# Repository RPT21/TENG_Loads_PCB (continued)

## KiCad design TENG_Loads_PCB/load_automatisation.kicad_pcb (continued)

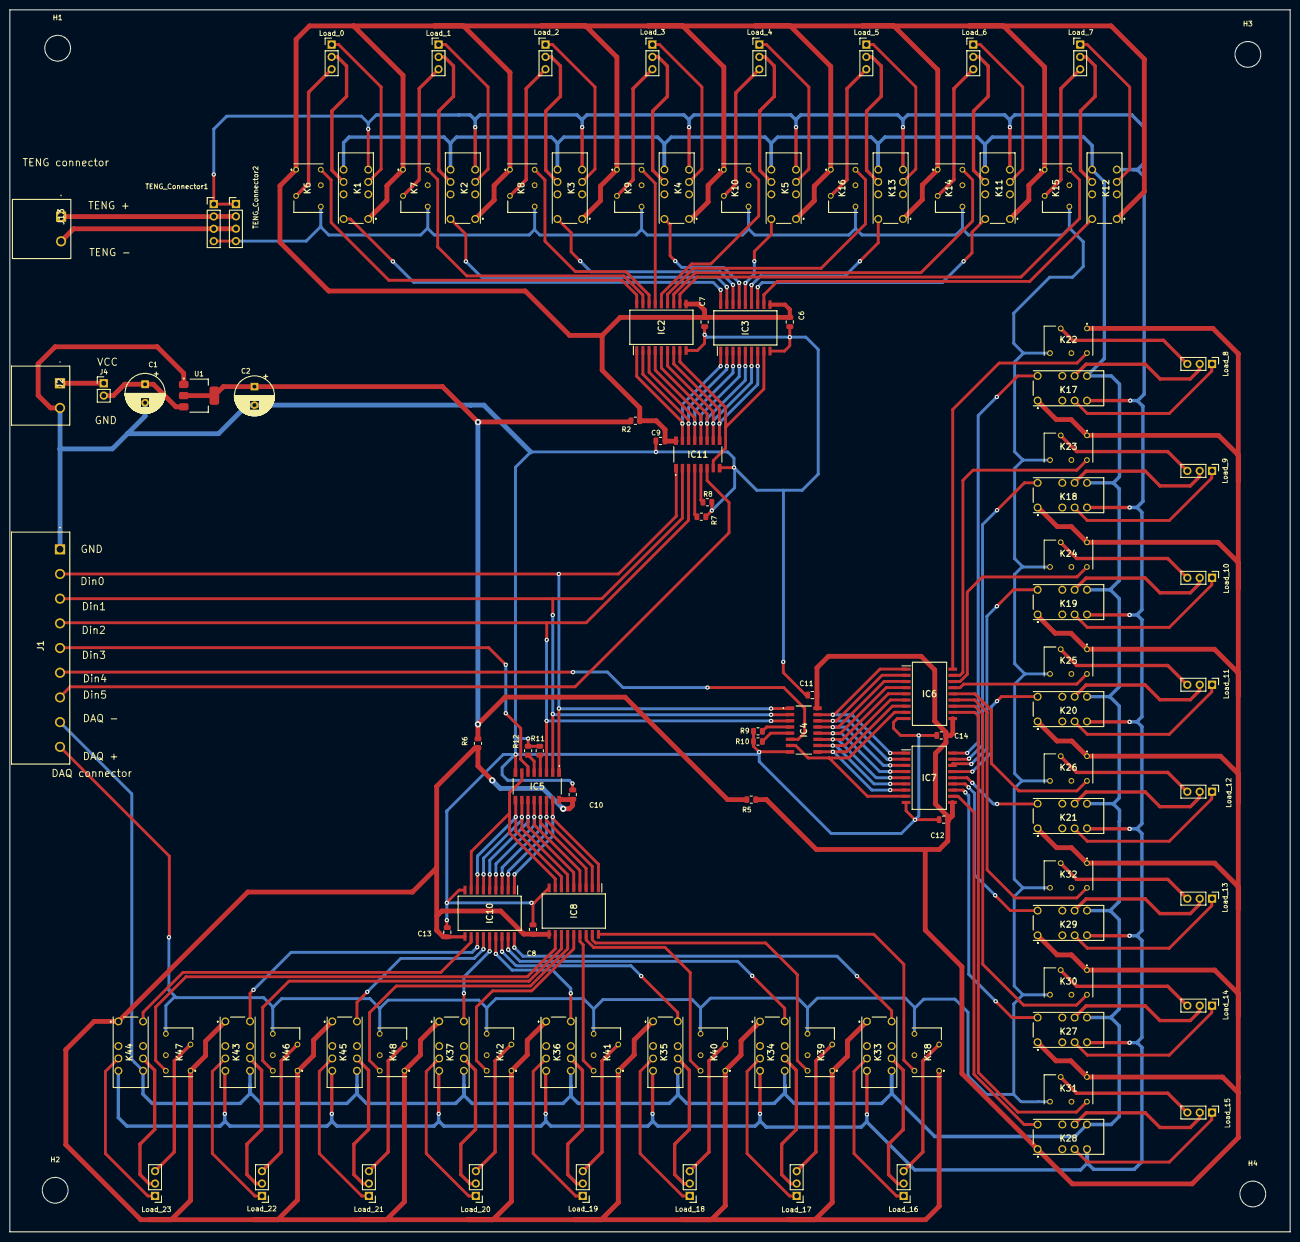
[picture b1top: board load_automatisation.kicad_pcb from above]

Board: 2 copper layers, 263.4 x 251.4 mm, 112 parts (0 on the bottom side), 168 nets.

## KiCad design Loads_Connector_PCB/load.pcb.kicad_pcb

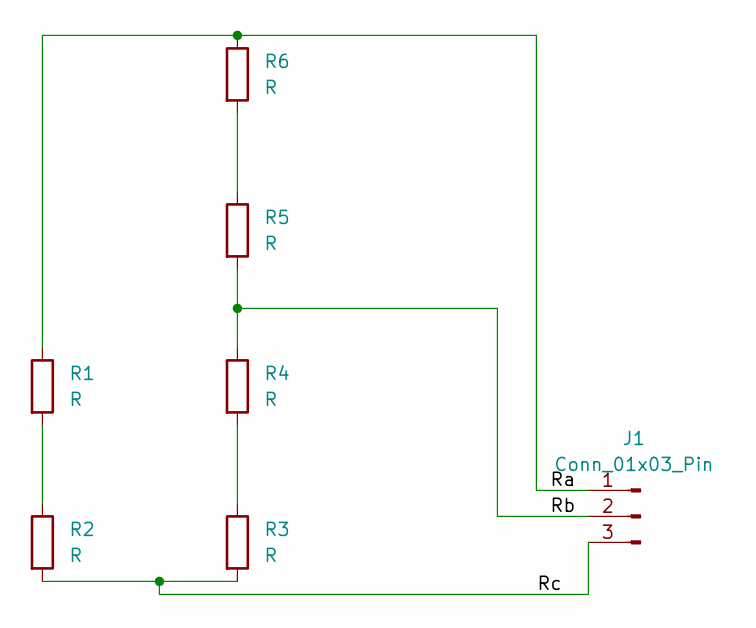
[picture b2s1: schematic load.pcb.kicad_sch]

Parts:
J1: Conn_01x03_Pin; PinHeader_1x03_P2.54mm_Horizontal
R1: R; R_Axial_DIN0614_L14.3mm_D5.7mm_P20.32mm_Horizontal
R2, R3, R4, R5, R6: R; R_0805_2012Metric

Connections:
/Ra: J1.1, R1.1, R6.1
/Rb: J1.2, R4.1, R5.2
/Rc: J1.3, R2.2, R3.2
unnamed: R1.2, R2.1
unnamed: R3.1, R4.2
unnamed: R5.1, R6.2

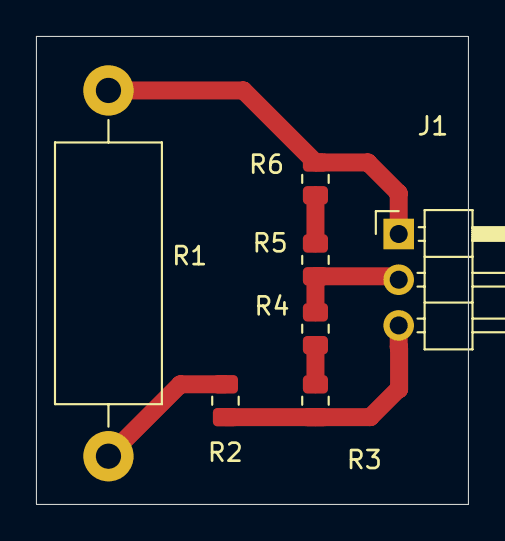
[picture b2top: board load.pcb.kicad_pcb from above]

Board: 2 copper layers, 24.0 x 26.0 mm, 7 parts (0 on the bottom side), 6 nets.

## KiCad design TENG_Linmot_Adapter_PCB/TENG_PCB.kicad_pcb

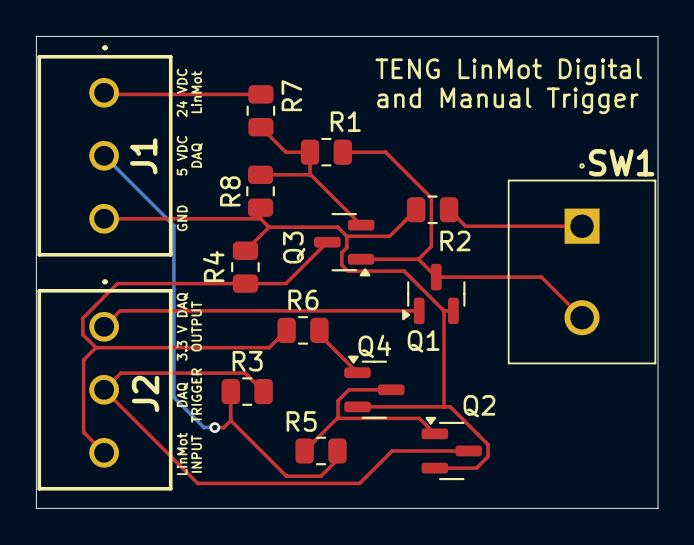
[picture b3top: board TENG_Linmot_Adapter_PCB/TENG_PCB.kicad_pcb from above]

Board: 2 copper layers, 34.5 x 26.2 mm, 15 parts (0 on the bottom side), 11 nets.

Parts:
J1, J2: 1751251
Q1, Q2, Q4: ZVN3310F; SOT-23
Q3: ZVP3310F; SOT-23
R1, R4, R6: 200K; R_0805_2012Metric
R2: 10K; R_0805_2012Metric
R3, R5: 100K; R_0805_2012Metric
R7: 5k; R_0805_2012Metric
R8: 15k; R_0805_2012Metric
SW1: SW_DIP_x01; 1729128

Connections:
5VDC_DAQ: J1.2, R3.1, R5.1
18VDC: Q3.2 (S), R1.1, R7.2, R8.1
+24V: J1.1, R7.1
DAQ_OUT_3.3V: J2.1, Q1.1 (G)
DAQ_TRIGGER: J2.2, Q2.3 (D), R3.2
GND: J1.3, Q1.2 (S), Q2.2 (S), Q4.2 (S), R2.2, R4.2, R8.2
LinMot_IN: J2.3, Q3.3 (D), R4.1, R6.1
unnamed: Q1.3 (D), Q3.1 (G), R1.2, SW1.2
unnamed: Q2.1 (G), Q4.3 (D), R5.2
unnamed: Q4.1 (G), R6.2
unnamed: R2.1, SW1.1

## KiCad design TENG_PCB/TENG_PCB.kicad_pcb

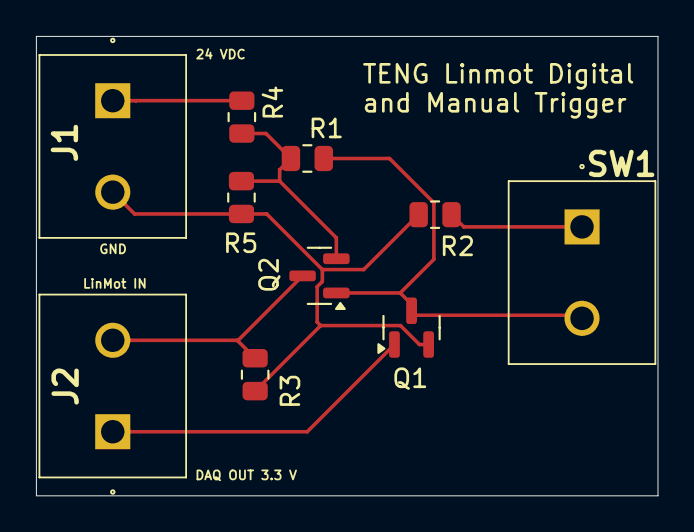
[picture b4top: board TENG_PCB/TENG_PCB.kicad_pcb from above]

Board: 2 copper layers, 34.5 x 25.5 mm, 10 parts (0 on the bottom side), 7 nets.

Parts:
J1, J2: 1729128
Q1: ZVN3310F; SOT-23
Q2: ZVP3310F; SOT-23
R1, R3: 200K; R_0805_2012Metric
R2: 10K; R_0805_2012Metric
R4: 5k; R_0805_2012Metric
R5: 15k; R_0805_2012Metric
SW1: SW_DIP_x01; 1729128

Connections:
18VDC: Q2.2 (S), R1.1, R4.2, R5.1
+24V: J1.1, R4.1
DAQ_OUT_3.3V: J2.1, Q1.1 (G)
GND: J1.2, Q1.2 (S), R2.2, R3.2, R5.2
LinMot_IN: J2.2, Q2.3 (D), R3.1
unnamed: Q1.3 (D), Q2.1 (G), R1.2, SW1.2
unnamed: R2.1, SW1.1

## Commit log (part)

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2025-03-26 First Commit
    PCB Design
2025-03-26 Changed Relay identifier
    Changed relay identifier with the correct one (12 VDC changed to 5 VDC).
2025-03-31 Capacitor and relay changes
    Capacitor correction and relay ID correction
2025-04-07 Updated connections
2025-04-10 Pull Down Resistor and reconnect
    Introduced the pull down resistors and reconnect all the unconnected tracks. The position of some items has changed to fit the new components.
2025-04-10 Little adjustments
    Little adjustments: Position correction in jumper
2025-04-10 Fix TENg buffer, ans some placements
2025-04-10 Fix ground pin, change sheet name, move 2 silkscreen labels
    1) Sheet name : Root
    2) Changed the position of 2 silkscreen labels
    3) Connect unconnected ground
2025-04-10 Upload Trigger TENG PCB
    First Commit of Trigger TENG PCB
2025-04-10 Upload gerber/drill files
    Uploading generated gerber and drill files.
2025-04-10 Added GND Silk Screen
    Added GND Silk Screen
2025-04-11 Update TENG trigger PCB
    Add trigger input ideas.
2025-06-05 Adding 3D models
    Add 3D models
2025-06-05 Adding 3D models
    Adding 3D models
2025-06-05 Update path 3D model
    Update path
2025-06-05 3D Model bug fixes
    Now it displays correctly the 3D model
2025-06-24 Solve 3D model bugs and add new models
    Solve 3D model bugs and add new models.
